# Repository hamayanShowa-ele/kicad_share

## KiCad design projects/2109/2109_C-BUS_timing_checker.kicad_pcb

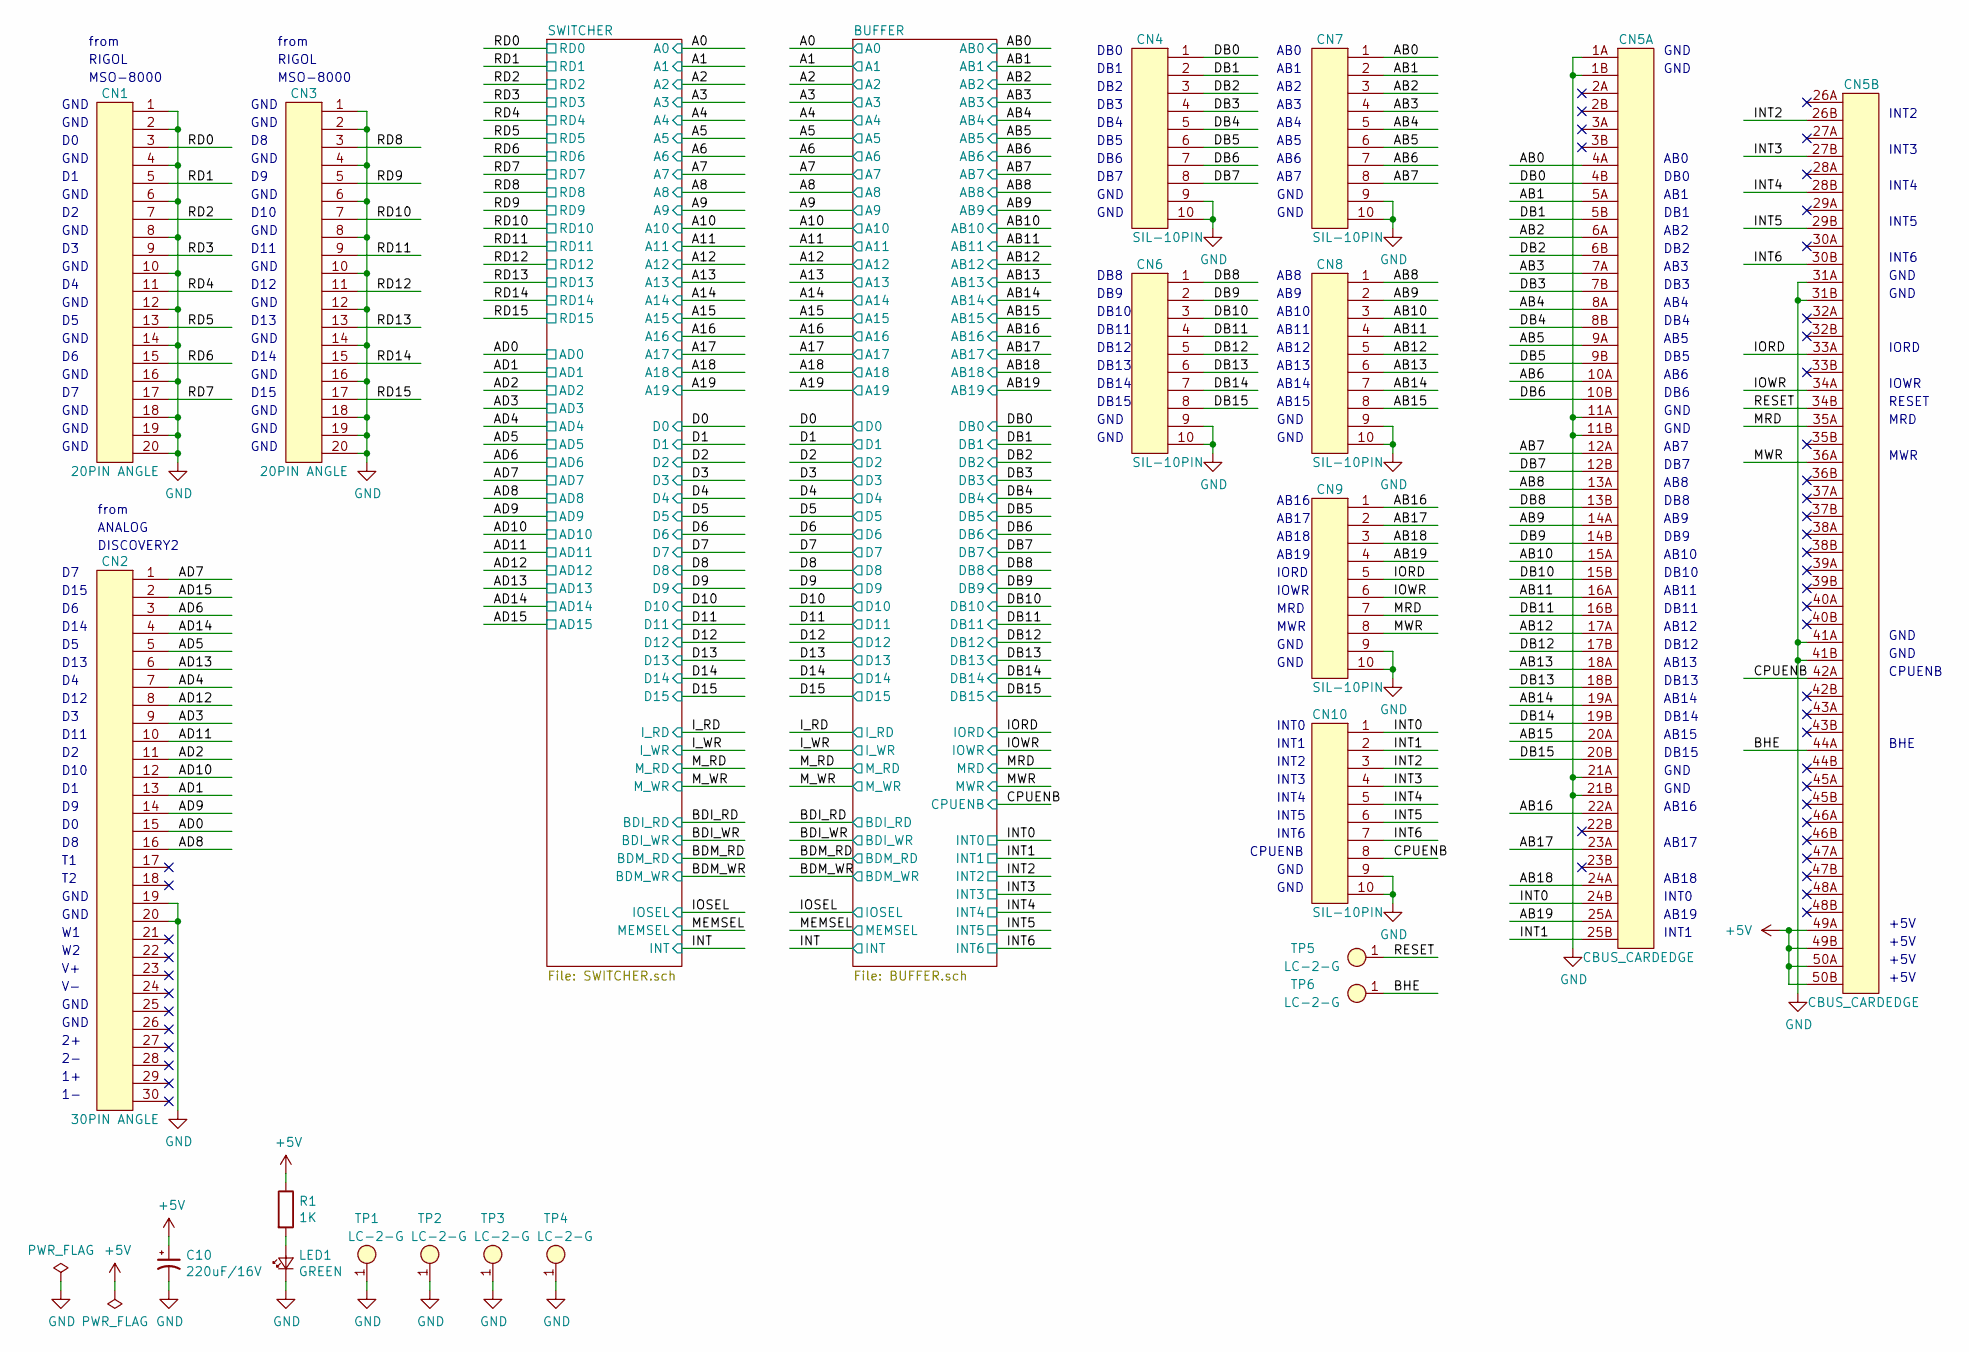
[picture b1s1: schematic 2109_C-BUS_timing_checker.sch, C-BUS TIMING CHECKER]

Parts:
C10: 220uF/16V; CP_Radial_D6.50mm_P2.50mm
CN1, CN3: 20PIN ANGLE; cn_HIF3FC-20PA-254DS
CN2: 30PIN ANGLE; cn_HIF3FC-30PA-254DS
CN4, CN6, CN7, CN8, CN9, CN10: SIL-10PIN; Pin_Header_Straight_1x10_Pitch2.54mm
CN5: CBUS_CARDEDGE; cn_CBUS_CARDEDGE
LED1: GREEN; C_0603
R1: 1K; C_0603
TP1, TP2, TP3, TP4, TP5, TP6: LC-2-G; tp_LC-2-G

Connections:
+5V: C10.1, CN5.49A, CN5.49B, CN5.50A, CN5.50B, R1.1; also elsewhere on the board
/AB0: CN5.4A, CN7.1; also elsewhere on the board
/AB1: CN5.5A, CN7.2; also elsewhere on the board
/AB2: CN5.6A, CN7.3; also elsewhere on the board
/AB3: CN5.7A, CN7.4; also elsewhere on the board
/AB4: CN5.8A, CN7.5; also elsewhere on the board
/AB5: CN5.9A, CN7.6; also elsewhere on the board
/AB6: CN5.10A, CN7.7; also elsewhere on the board
/AB7: CN5.12A, CN7.8; also elsewhere on the board
/AB8: CN5.13A, CN8.1; also elsewhere on the board
/AB9: CN5.14A, CN8.2; also elsewhere on the board
/AB10: CN5.15A, CN8.3; also elsewhere on the board
/AB11: CN5.16A, CN8.4; also elsewhere on the board
/AB12: CN5.17A, CN8.5; also elsewhere on the board
/AB13: CN5.18A, CN8.6; also elsewhere on the board
/AB14: CN5.19A, CN8.7; also elsewhere on the board
/AB15: CN5.20A, CN8.8; also elsewhere on the board
/AB16: CN5.22A, CN9.1; also elsewhere on the board
/AB17: CN5.23A, CN9.2; also elsewhere on the board
/AB18: CN5.24A, CN9.3; also elsewhere on the board
/AB19: CN5.25A, CN9.4; also elsewhere on the board
/AD0: CN2.15; also elsewhere on the board
/AD1: CN2.13; also elsewhere on the board
/AD2: CN2.11; also elsewhere on the board
/AD3: CN2.9; also elsewhere on the board
/AD4: CN2.7; also elsewhere on the board
/AD5: CN2.5; also elsewhere on the board
/AD6: CN2.3; also elsewhere on the board
/AD7: CN2.1; also elsewhere on the board
/AD8: CN2.16; also elsewhere on the board
/AD9: CN2.14; also elsewhere on the board
/AD10: CN2.12; also elsewhere on the board
/AD11: CN2.10; also elsewhere on the board
/AD12: CN2.8; also elsewhere on the board
/AD13: CN2.6; also elsewhere on the board
/AD14: CN2.4; also elsewhere on the board
/AD15: CN2.2; also elsewhere on the board
/BHE: CN5.44A, TP6.1
/CPUENB: CN5.42A, CN10.8; also elsewhere on the board
/DB0: CN4.1, CN5.4B; also elsewhere on the board
/DB1: CN4.2, CN5.5B; also elsewhere on the board
/DB2: CN4.3, CN5.6B; also elsewhere on the board
/DB3: CN4.4, CN5.7B; also elsewhere on the board
/DB4: CN4.5, CN5.8B; also elsewhere on the board
/DB5: CN4.6, CN5.9B; also elsewhere on the board
/DB6: CN4.7, CN5.10B; also elsewhere on the board
/DB7: CN4.8, CN5.12B; also elsewhere on the board
/DB8: CN5.13B, CN6.1; also elsewhere on the board
/DB9: CN5.14B, CN6.2; also elsewhere on the board
/DB10: CN5.15B, CN6.3; also elsewhere on the board
/DB11: CN5.16B, CN6.4; also elsewhere on the board
/DB12: CN5.17B, CN6.5; also elsewhere on the board
/DB13: CN5.18B, CN6.6; also elsewhere on the board
/DB14: CN5.19B, CN6.7; also elsewhere on the board
/DB15: CN5.20B, CN6.8; also elsewhere on the board
/INT0: CN5.24B, CN10.1; also elsewhere on the board
/INT1: CN5.25B, CN10.2; also elsewhere on the board
/INT2: CN5.26B, CN10.3; also elsewhere on the board
/INT3: CN5.27B, CN10.4; also elsewhere on the board
/INT4: CN5.28B, CN10.5; also elsewhere on the board
/INT5: CN5.29B, CN10.6; also elsewhere on the board
/INT6: CN5.30B, CN10.7; also elsewhere on the board
/IORD: CN5.33A, CN9.5; also elsewhere on the board
/IOWR: CN5.34A, CN9.6; also elsewhere on the board
/MRD: CN5.35A, CN9.7; also elsewhere on the board
/MWR: CN5.36A, CN9.8; also elsewhere on the board
/RD0: CN1.3; also elsewhere on the board
/RD1: CN1.5; also elsewhere on the board
/RD2: CN1.7; also elsewhere on the board
/RD3: CN1.9; also elsewhere on the board
/RD4: CN1.11; also elsewhere on the board
/RD5: CN1.13; also elsewhere on the board
/RD6: CN1.15; also elsewhere on the board
/RD7: CN1.17; also elsewhere on the board
/RD8: CN3.3; also elsewhere on the board
/RD9: CN3.5; also elsewhere on the board
/RD10: CN3.7; also elsewhere on the board
/RD11: CN3.9; also elsewhere on the board
/RD12: CN3.11; also elsewhere on the board
/RD13: CN3.13; also elsewhere on the board
/RD14: CN3.15; also elsewhere on the board
/RD15: CN3.17; also elsewhere on the board
/RESET: CN5.34B, TP5.1
GND: C10.2, CN1.1, CN1.2, CN1.4, CN1.6, CN1.8, CN1.10, CN1.12, CN1.14, CN1.16, CN1.18, CN1.19, CN1.20, CN2.19, CN2.20, CN3.1, CN3.2, CN3.4, CN3.6, CN3.8, CN3.10, CN3.12, CN3.14, CN3.16, CN3.18, CN3.19, CN3.20, CN4.9, CN4.10, CN5.1A, CN5.1B, CN5.11A, CN5.11B, CN5.21A, CN5.21B, CN5.31A, CN5.31B, CN5.41A, CN5.41B, CN6.9, CN6.10, CN7.9, CN7.10, CN8.9, CN8.10, CN9.9, CN9.10, CN10.9, CN10.10, LED1.2 (K), TP1.1, TP2.1, TP3.1, TP4.1; also elsewhere on the board
unnamed: LED1.1 (A), R1.2

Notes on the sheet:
GND
+5V
AB0
AB1
DB0
AB2
AB3
AB4
AB5
AB6
AB7
AB8
AB9
AB10
AB11
AB12
AB13
AB14
AB15
AB16
AB17
AB18
AB19
DB1
DB2
DB3
DB4
DB5
DB6
DB7
DB8
DB9
DB10
DB11
DB12
DB13
DB14
DB15
INT1
INT0

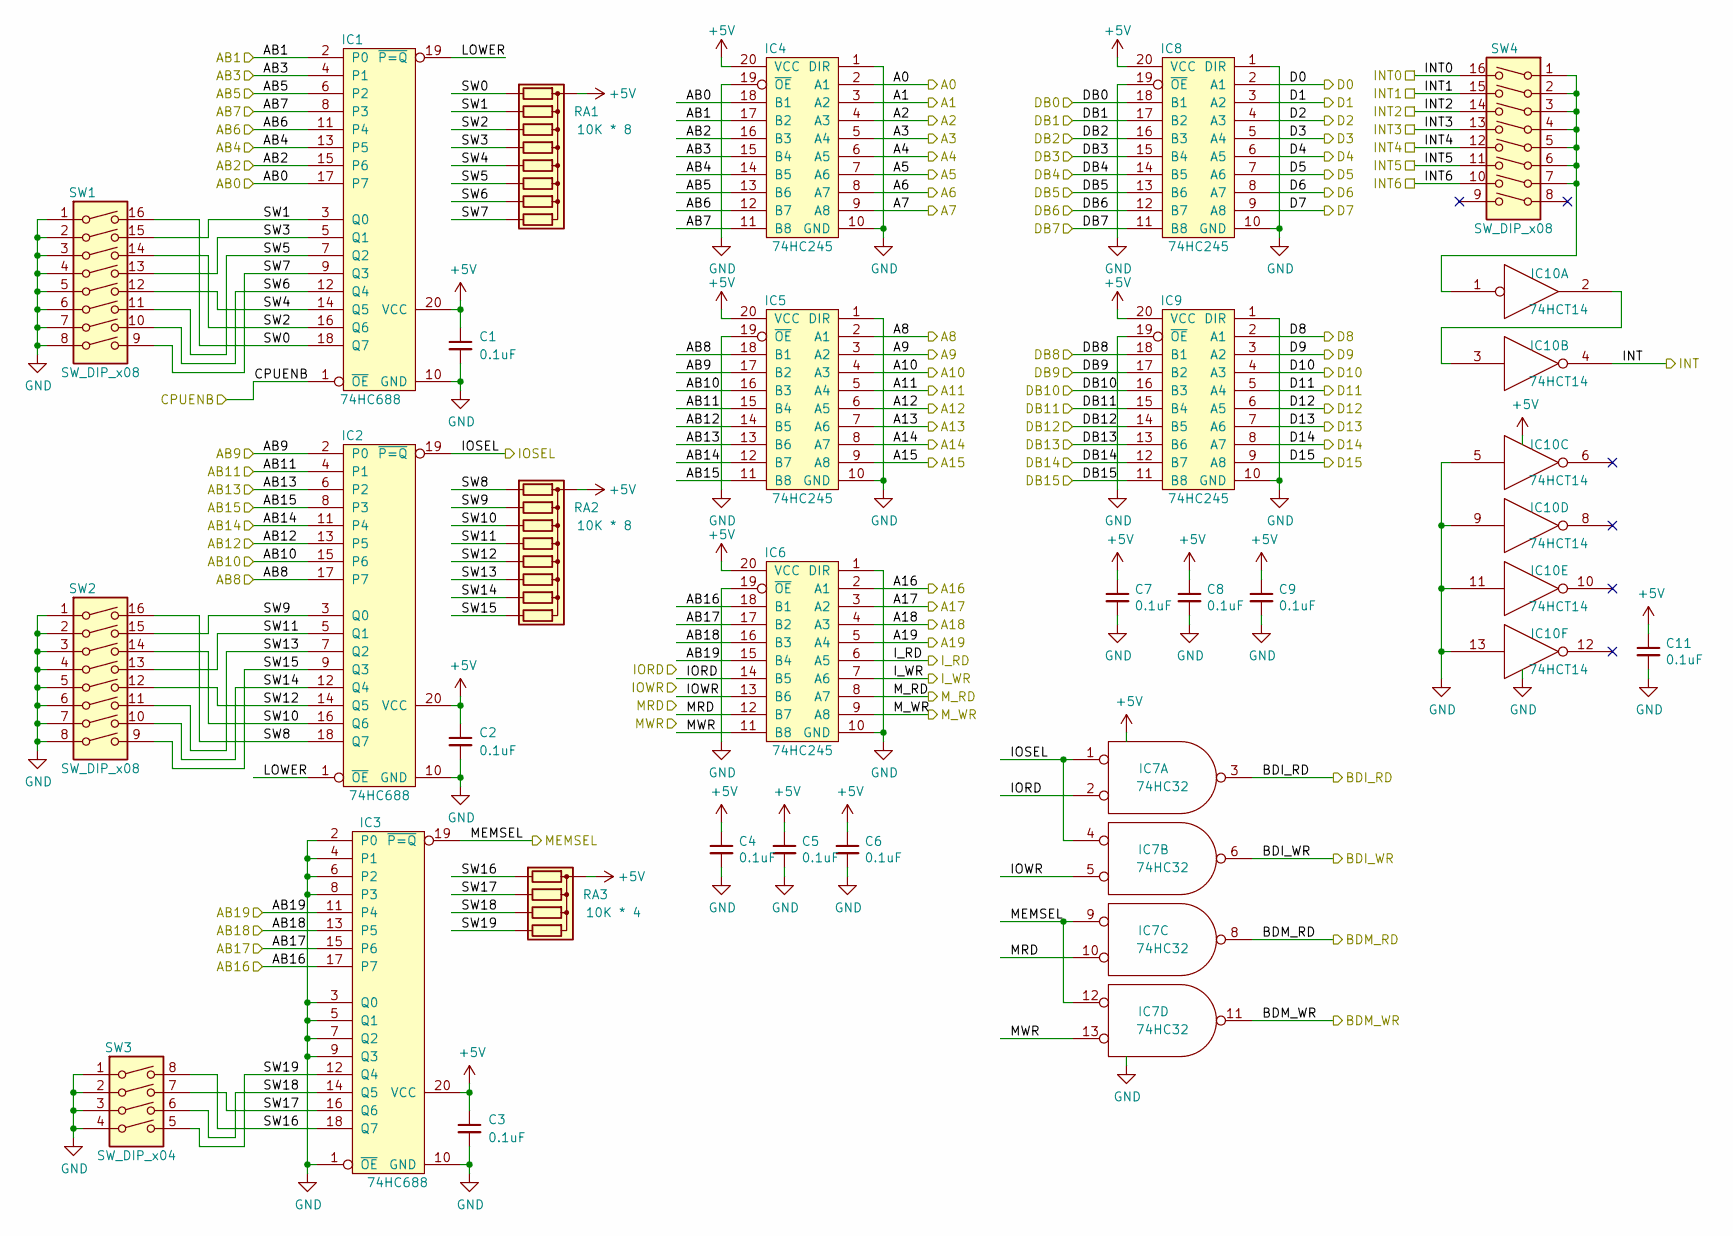
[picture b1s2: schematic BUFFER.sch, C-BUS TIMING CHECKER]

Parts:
C1, C2, C3, C4, C5, C6, C7, C8, C9, C11: 0.1uF; C_0603
IC1, IC2, IC3: 74HC688; ic_DIP-20_W7.62mm
IC4, IC5, IC6, IC8, IC9: 74HC245; ic_DIP-20_W7.62mm
IC7: 74HC32; IC_DIP-14_W7.62mm
IC10: 74HCT14; IC_DIP-14_W7.62mm
RA1, RA2: 10K * 8; ra_RKC1_8B8
RA3: 10K * 4; ra_RKC1_8B4
SW1, SW2, SW4: SW_DIP_x08; ic_DIP-16_W7.62mm
SW3: SW_DIP_x04; ic_DIP-8_W7.62mm

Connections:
+5V: C1.1, C2.1, C3.1, C4.1, C5.1, C6.1, C7.1, C8.1, C9.1, C11.1, IC1.20 (VCC), IC2.20 (VCC), IC3.20 (VCC), IC4.20 (VCC), IC5.20 (VCC), IC6.20 (VCC), IC7.14 (+5V), IC8.20 (VCC), IC9.20 (VCC), IC10.14 (+5V), RA1.1 (common), RA2.1 (common), RA3.1 (common); also elsewhere on the board
/A0: IC4.2 (A1); also elsewhere on the board
/A1: IC4.3 (A2); also elsewhere on the board
/A2: IC4.4 (A3); also elsewhere on the board
/A3: IC4.5 (A4); also elsewhere on the board
/A4: IC4.6 (A5); also elsewhere on the board
/A5: IC4.7 (A6); also elsewhere on the board
/A6: IC4.8 (A7); also elsewhere on the board
/A7: IC4.9 (A8); also elsewhere on the board
/A8: IC5.2 (A1); also elsewhere on the board
/A9: IC5.3 (A2); also elsewhere on the board
/A10: IC5.4 (A3); also elsewhere on the board
/A11: IC5.5 (A4); also elsewhere on the board
/A12: IC5.6 (A5); also elsewhere on the board
/A13: IC5.7 (A6); also elsewhere on the board
/A14: IC5.8 (A7); also elsewhere on the board
/A15: IC5.9 (A8); also elsewhere on the board
/A16: IC6.2 (A1); also elsewhere on the board
/A17: IC6.3 (A2); also elsewhere on the board
/A18: IC6.4 (A3); also elsewhere on the board
/A19: IC6.5 (A4); also elsewhere on the board
/AB0: IC1.17 (P7), IC4.18 (B1); also elsewhere on the board
/AB1: IC1.2 (P0), IC4.17 (B2); also elsewhere on the board
/AB2: IC1.15 (P6), IC4.16 (B3); also elsewhere on the board
/AB3: IC1.4 (P1), IC4.15 (B4); also elsewhere on the board
/AB4: IC1.13 (P5), IC4.14 (B5); also elsewhere on the board
/AB5: IC1.6 (P2), IC4.13 (B6); also elsewhere on the board
/AB6: IC1.11 (P4), IC4.12 (B7); also elsewhere on the board
/AB7: IC1.8 (P3), IC4.11 (B8); also elsewhere on the board
/AB8: IC2.17 (P7), IC5.18 (B1); also elsewhere on the board
/AB9: IC2.2 (P0), IC5.17 (B2); also elsewhere on the board
/AB10: IC2.15 (P6), IC5.16 (B3); also elsewhere on the board
/AB11: IC2.4 (P1), IC5.15 (B4); also elsewhere on the board
/AB12: IC2.13 (P5), IC5.14 (B5); also elsewhere on the board
/AB13: IC2.6 (P2), IC5.13 (B6); also elsewhere on the board
/AB14: IC2.11 (P4), IC5.12 (B7); also elsewhere on the board
/AB15: IC2.8 (P3), IC5.11 (B8); also elsewhere on the board
/AB16: IC3.17 (P7), IC6.18 (B1); also elsewhere on the board
/AB17: IC3.15 (P6), IC6.17 (B2); also elsewhere on the board
/AB18: IC3.13 (P5), IC6.16 (B3); also elsewhere on the board
/AB19: IC3.11 (P4), IC6.15 (B4); also elsewhere on the board
/BDI_RD: IC7.3; also elsewhere on the board
/BDI_WR: IC7.6; also elsewhere on the board
/BDM_RD: IC7.8; also elsewhere on the board
/BDM_WR: IC7.11; also elsewhere on the board
/BUFFER/LOWER: IC1.19 (~P=Q), IC2.1 (~OE)
/BUFFER/SW0: IC1.18 (Q7), RA1.2 (R1), SW1.16
/BUFFER/SW1: IC1.3 (Q0), RA1.3 (R2), SW1.15
/BUFFER/SW2: IC1.16 (Q6), RA1.4 (R3), SW1.14
/BUFFER/SW3: IC1.5 (Q1), RA1.5 (R4), SW1.13
/BUFFER/SW4: IC1.14 (Q5), RA1.6 (R5), SW1.12
/BUFFER/SW5: IC1.7 (Q2), RA1.7 (R6), SW1.11
/BUFFER/SW6: IC1.12 (Q4), RA1.8 (R7), SW1.10
/BUFFER/SW7: IC1.9 (Q3), RA1.9 (R8), SW1.9
/BUFFER/SW8: IC2.18 (Q7), RA2.2 (R1), SW2.16
/BUFFER/SW9: IC2.3 (Q0), RA2.3 (R2), SW2.15
/BUFFER/SW10: IC2.16 (Q6), RA2.4 (R3), SW2.14
/BUFFER/SW11: IC2.5 (Q1), RA2.5 (R4), SW2.13
/BUFFER/SW12: IC2.14 (Q5), RA2.6 (R5), SW2.12
/BUFFER/SW13: IC2.7 (Q2), RA2.7 (R6), SW2.11
/BUFFER/SW14: IC2.12 (Q4), RA2.8 (R7), SW2.10
/BUFFER/SW15: IC2.9 (Q3), RA2.9 (R8), SW2.9
/BUFFER/SW16: IC3.18 (Q7), RA3.2 (R1), SW3.8
/BUFFER/SW17: IC3.16 (Q6), RA3.3 (R2), SW3.7
/BUFFER/SW18: IC3.14 (Q5), RA3.4 (R3), SW3.6
/BUFFER/SW19: IC3.12 (Q4), RA3.5 (R4), SW3.5
/CPUENB: IC1.1 (~OE); also elsewhere on the board
/D0: IC8.2 (A1); also elsewhere on the board
/D1: IC8.3 (A2); also elsewhere on the board
/D2: IC8.4 (A3); also elsewhere on the board
/D3: IC8.5 (A4); also elsewhere on the board
/D4: IC8.6 (A5); also elsewhere on the board
/D5: IC8.7 (A6); also elsewhere on the board
/D6: IC8.8 (A7); also elsewhere on the board
/D7: IC8.9 (A8); also elsewhere on the board
/D8: IC9.2 (A1); also elsewhere on the board
/D9: IC9.3 (A2); also elsewhere on the board
/D10: IC9.4 (A3); also elsewhere on the board
/D11: IC9.5 (A4); also elsewhere on the board
/D12: IC9.6 (A5); also elsewhere on the board
/D13: IC9.7 (A6); also elsewhere on the board
/D14: IC9.8 (A7); also elsewhere on the board
/D15: IC9.9 (A8); also elsewhere on the board
/DB0: IC8.18 (B1); also elsewhere on the board
/DB1: IC8.17 (B2); also elsewhere on the board
/DB2: IC8.16 (B3); also elsewhere on the board
/DB3: IC8.15 (B4); also elsewhere on the board
/DB4: IC8.14 (B5); also elsewhere on the board
/DB5: IC8.13 (B6); also elsewhere on the board
/DB6: IC8.12 (B7); also elsewhere on the board
/DB7: IC8.11 (B8); also elsewhere on the board
/DB8: IC9.18 (B1); also elsewhere on the board
/DB9: IC9.17 (B2); also elsewhere on the board
/DB10: IC9.16 (B3); also elsewhere on the board
/DB11: IC9.15 (B4); also elsewhere on the board
/DB12: IC9.14 (B5); also elsewhere on the board
/DB13: IC9.13 (B6); also elsewhere on the board
/DB14: IC9.12 (B7); also elsewhere on the board
/DB15: IC9.11 (B8); also elsewhere on the board
/INT: IC10.4; also elsewhere on the board
/INT0: SW4.16; also elsewhere on the board
/INT1: SW4.15; also elsewhere on the board
/INT2: SW4.14; also elsewhere on the board
/INT3: SW4.13; also elsewhere on the board
/INT4: SW4.12; also elsewhere on the board
/INT5: SW4.11; also elsewhere on the board
/INT6: SW4.10; also elsewhere on the board
/IORD: IC6.14 (B5), IC7.2; also elsewhere on the board
/IOSEL: IC2.19 (~P=Q), IC7.1, IC7.4; also elsewhere on the board
/IOWR: IC6.13 (B6), IC7.5; also elsewhere on the board
/I_RD: IC6.6 (A5); also elsewhere on the board
/I_WR: IC6.7 (A6); also elsewhere on the board
/MEMSEL: IC3.19 (~P=Q), IC7.9, IC7.12; also elsewhere on the board
/MRD: IC6.12 (B7), IC7.10; also elsewhere on the board
/MWR: IC6.11 (B8), IC7.13; also elsewhere on the board
/M_RD: IC6.8 (A7); also elsewhere on the board
/M_WR: IC6.9 (A8); also elsewhere on the board
GND: C1.2, C2.2, C3.2, C4.2, C5.2, C6.2, C7.2, C8.2, C9.2, C11.2, IC1.10 (GND), IC2.10 (GND), IC3.1 (~OE), IC3.2 (P0), IC3.3 (Q0), IC3.4 (P1), IC3.5 (Q1), IC3.6 (P2), IC3.7 (Q2), IC3.8 (P3), IC3.9 (Q3), IC3.10 (GND), IC4.1 (DIR), IC4.10 (GND), IC4.19 (~OE), IC5.1 (DIR), IC5.10 (GND), IC5.19 (~OE), IC6.1 (DIR), IC6.10 (GND), IC6.19 (~OE), IC7.7 (GND), IC8.1 (DIR), IC8.10 (GND), IC8.19 (~OE), IC9.1 (DIR), IC9.10 (GND), IC9.19 (~OE), IC10.5, IC10.7 (GND), IC10.9, IC10.11, IC10.13, SW1.1, SW1.2, SW1.3, SW1.4, SW1.5, SW1.6, SW1.7, SW1.8, SW2.1, SW2.2, SW2.3, SW2.4, SW2.5, SW2.6, SW2.7, SW2.8, SW3.1, SW3.2, SW3.3, SW3.4; also elsewhere on the board
unnamed: IC10.1, SW4.1, SW4.2, SW4.3, SW4.4, SW4.5, SW4.6, SW4.7
unnamed: IC10.2, IC10.3

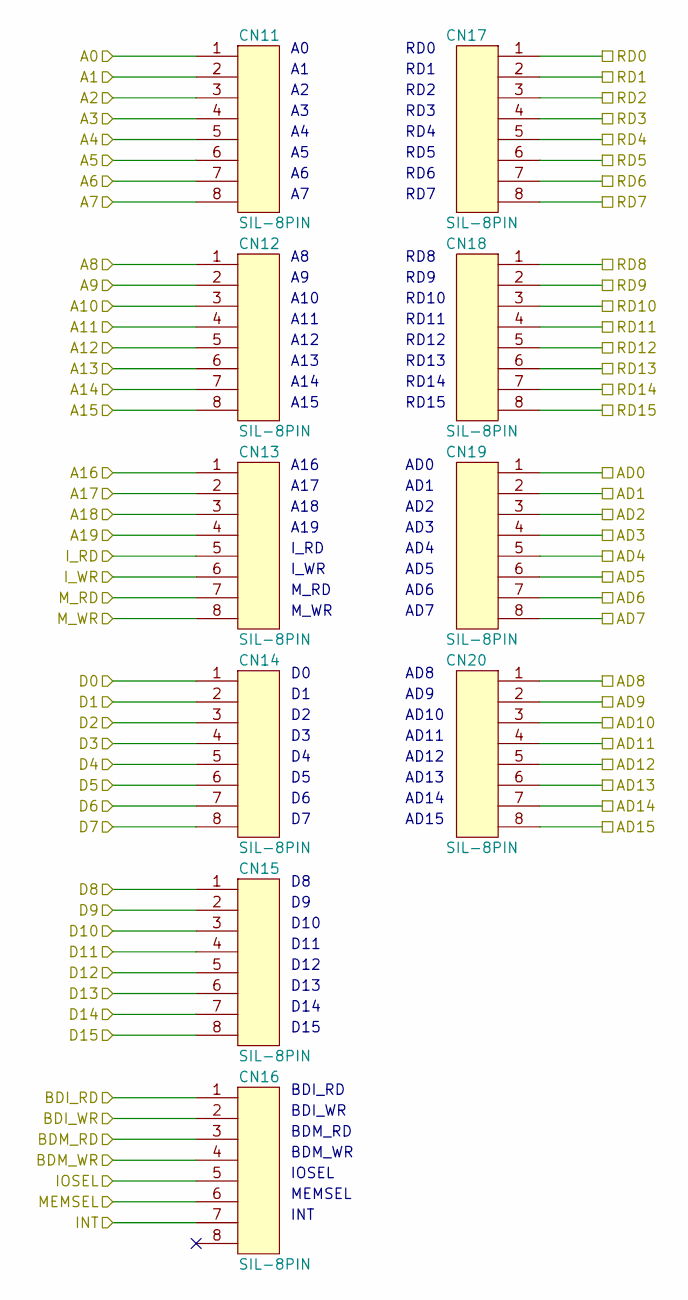
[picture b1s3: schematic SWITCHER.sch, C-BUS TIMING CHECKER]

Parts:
CN11, CN12, CN13, CN14, CN15, CN16, CN17, CN18, CN19, CN20: SIL-8PIN; Pin_Header_Straight_1x08_Pitch2.54mm

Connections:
/A0: CN11.1; also elsewhere on the board
/A1: CN11.2; also elsewhere on the board
/A2: CN11.3; also elsewhere on the board
/A3: CN11.4; also elsewhere on the board
/A4: CN11.5; also elsewhere on the board
/A5: CN11.6; also elsewhere on the board
/A6: CN11.7; also elsewhere on the board
/A7: CN11.8; also elsewhere on the board
/A8: CN12.1; also elsewhere on the board
/A9: CN12.2; also elsewhere on the board
/A10: CN12.3; also elsewhere on the board
/A11: CN12.4; also elsewhere on the board
/A12: CN12.5; also elsewhere on the board
/A13: CN12.6; also elsewhere on the board
/A14: CN12.7; also elsewhere on the board
/A15: CN12.8; also elsewhere on the board
/A16: CN13.1; also elsewhere on the board
/A17: CN13.2; also elsewhere on the board
/A18: CN13.3; also elsewhere on the board
/A19: CN13.4; also elsewhere on the board
/AD0: CN19.1; also elsewhere on the board
/AD1: CN19.2; also elsewhere on the board
/AD2: CN19.3; also elsewhere on the board
/AD3: CN19.4; also elsewhere on the board
/AD4: CN19.5; also elsewhere on the board
/AD5: CN19.6; also elsewhere on the board
/AD6: CN19.7; also elsewhere on the board
/AD7: CN19.8; also elsewhere on the board
/AD8: CN20.1; also elsewhere on the board
/AD9: CN20.2; also elsewhere on the board
/AD10: CN20.3; also elsewhere on the board
/AD11: CN20.4; also elsewhere on the board
/AD12: CN20.5; also elsewhere on the board
/AD13: CN20.6; also elsewhere on the board
/AD14: CN20.7; also elsewhere on the board
/AD15: CN20.8; also elsewhere on the board
/BDI_RD: CN16.1; also elsewhere on the board
/BDI_WR: CN16.2; also elsewhere on the board
/BDM_RD: CN16.3; also elsewhere on the board
/BDM_WR: CN16.4; also elsewhere on the board
/D0: CN14.1; also elsewhere on the board
/D1: CN14.2; also elsewhere on the board
/D2: CN14.3; also elsewhere on the board
/D3: CN14.4; also elsewhere on the board
/D4: CN14.5; also elsewhere on the board
/D5: CN14.6; also elsewhere on the board
/D6: CN14.7; also elsewhere on the board
/D7: CN14.8; also elsewhere on the board
/D8: CN15.1; also elsewhere on the board
/D9: CN15.2; also elsewhere on the board
/D10: CN15.3; also elsewhere on the board
/D11: CN15.4; also elsewhere on the board
/D12: CN15.5; also elsewhere on the board
/D13: CN15.6; also elsewhere on the board
/D14: CN15.7; also elsewhere on the board
/D15: CN15.8; also elsewhere on the board
/INT: CN16.7; also elsewhere on the board
/IOSEL: CN16.5; also elsewhere on the board
/I_RD: CN13.5; also elsewhere on the board
/I_WR: CN13.6; also elsewhere on the board
/MEMSEL: CN16.6; also elsewhere on the board
/M_RD: CN13.7; also elsewhere on the board
/M_WR: CN13.8; also elsewhere on the board
/RD0: CN17.1; also elsewhere on the board
/RD1: CN17.2; also elsewhere on the board
/RD2: CN17.3; also elsewhere on the board
/RD3: CN17.4; also elsewhere on the board
/RD4: CN17.5; also elsewhere on the board
/RD5: CN17.6; also elsewhere on the board
/RD6: CN17.7; also elsewhere on the board
/RD7: CN17.8; also elsewhere on the board
/RD8: CN18.1; also elsewhere on the board
/RD9: CN18.2; also elsewhere on the board
/RD10: CN18.3; also elsewhere on the board
/RD11: CN18.4; also elsewhere on the board
/RD12: CN18.5; also elsewhere on the board
/RD13: CN18.6; also elsewhere on the board
/RD14: CN18.7; also elsewhere on the board
/RD15: CN18.8; also elsewhere on the board

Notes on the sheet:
RD0
RD1
RD2
RD3
RD4
RD5
RD6
RD7
RD8
RD9
RD10
RD11
RD12
RD13
RD14
RD15
A10
A11
A12
A13
A14
A15
A16
A17
A18
A19
I_RD
I_WR
M_RD
M_WR
D10
D11
D12
D13
D14
D15
BDI_RD
BDI_WR
BDM_RD
BDM_WR

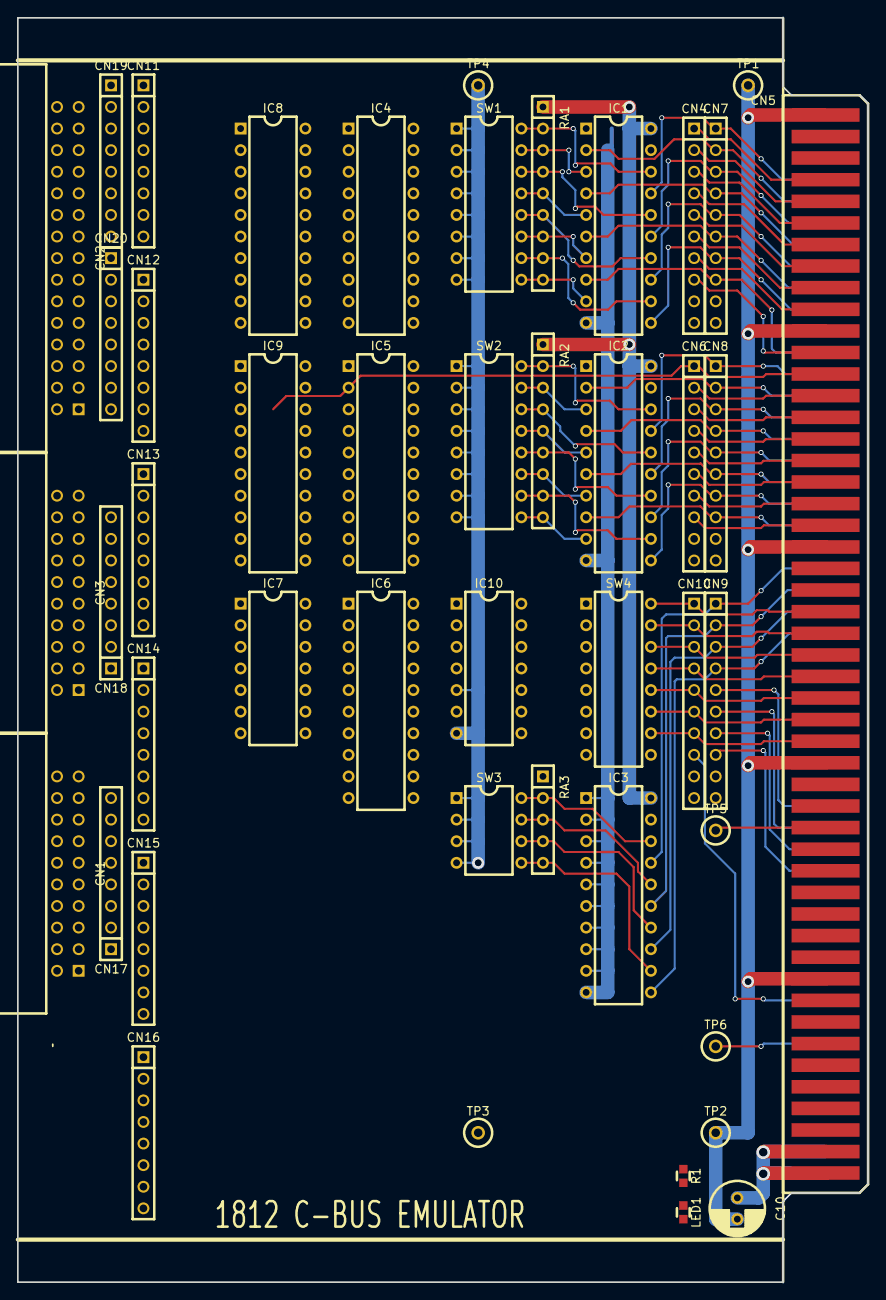
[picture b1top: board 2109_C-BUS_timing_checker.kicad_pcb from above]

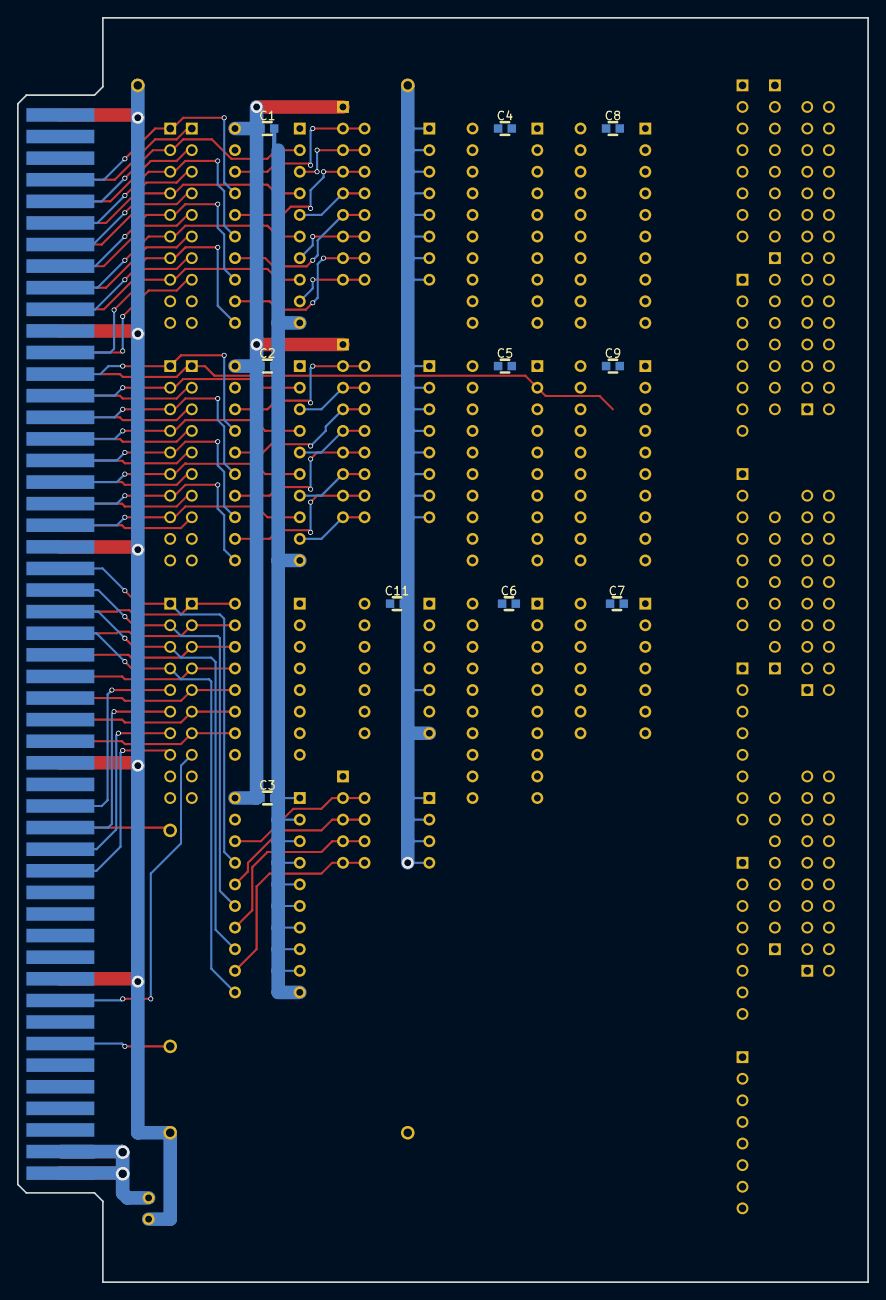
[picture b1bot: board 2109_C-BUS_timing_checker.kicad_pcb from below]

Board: 2 copper layers, 100.0 x 148.7 mm, 56 parts (10 on the bottom side), 155 nets.

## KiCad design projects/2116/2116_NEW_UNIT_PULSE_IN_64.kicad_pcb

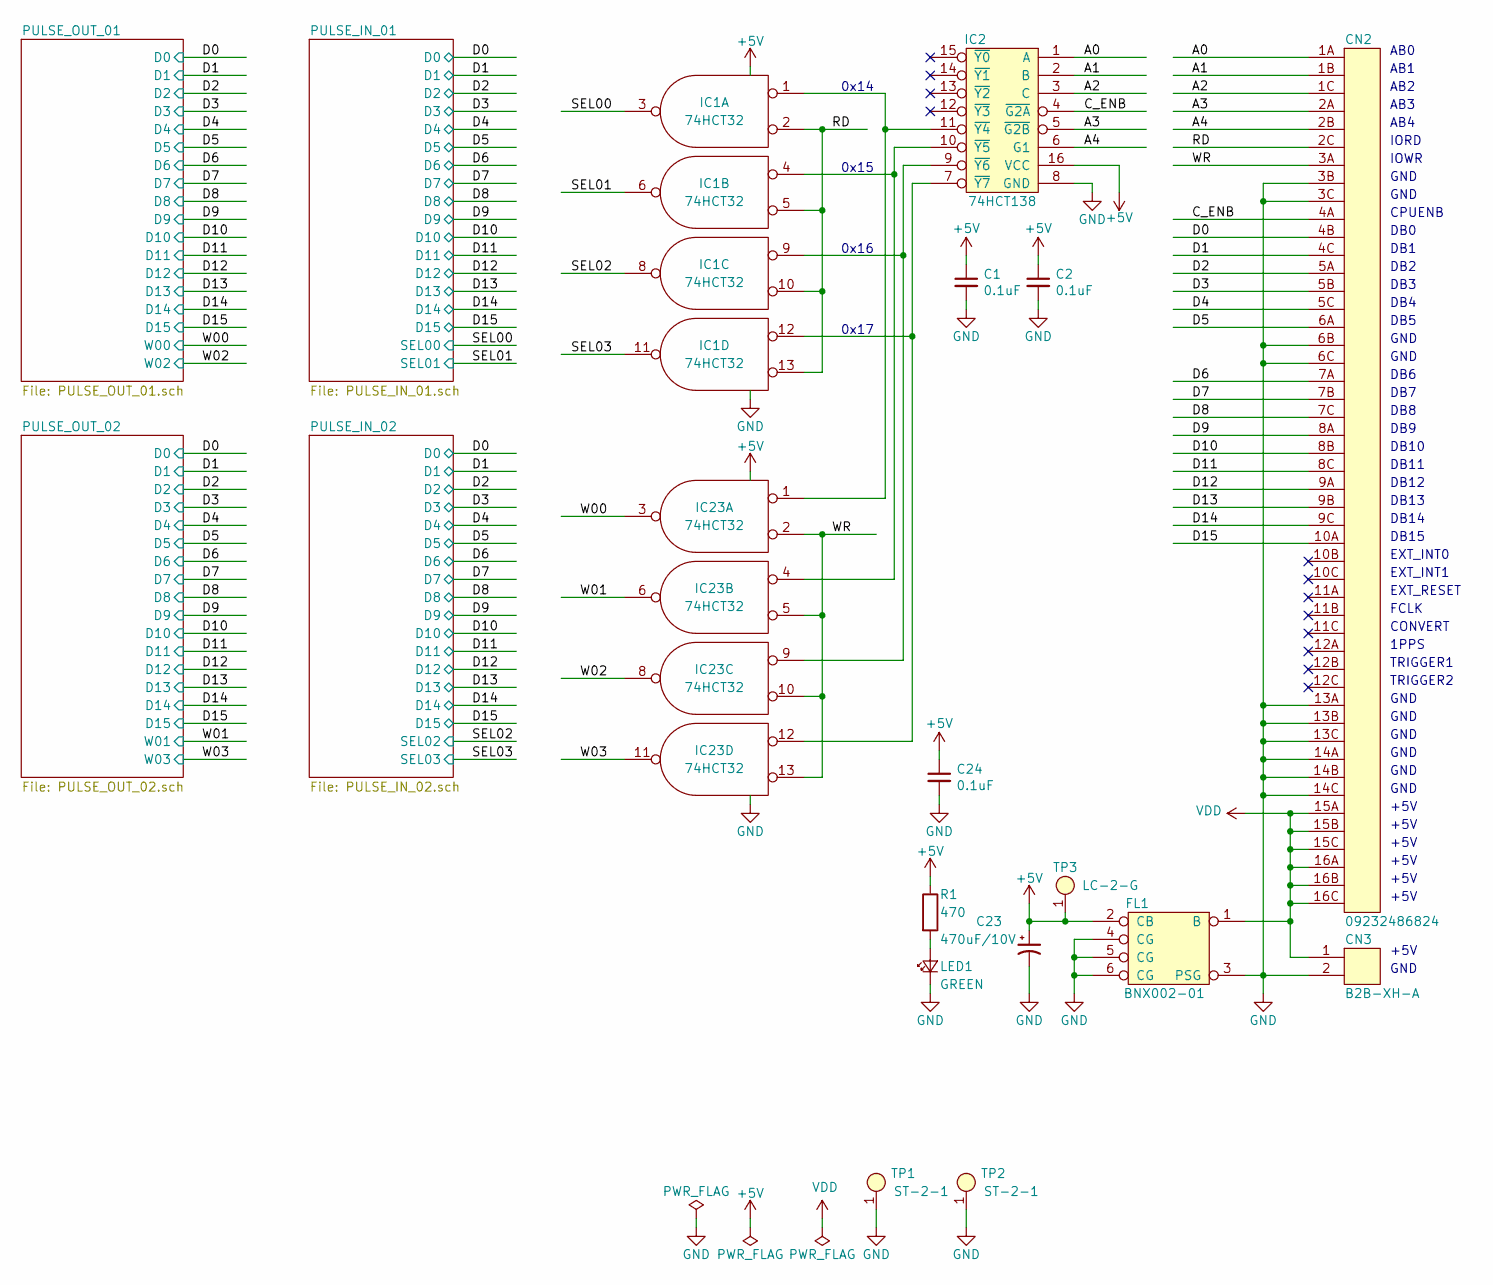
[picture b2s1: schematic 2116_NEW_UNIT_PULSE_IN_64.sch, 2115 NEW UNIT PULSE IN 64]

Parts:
C1, C2, C24: 0.1uF; C_0603
C23: 470uF/10V; CP_D8_P3R5
CN2: 09232486824; cn_09282486801
CN3: B2B-XH-A; cn_B2B-XH-A
FL1: BNX002-01
IC1, IC23: 74HCT32; IC_DIP-14_W7.62mm
IC2: 74HCT138; ic_DIP-16_W7.62mm
LED1: GREEN; LED_D3.0mm_center
R1: 470; R_TH_5R08
TP1, TP2: ST-2-1; LC-2-G
TP3: LC-2-G

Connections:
+5V: C1.1, C2.1, C23.1, C24.1, FL1.2 (CB), IC1.14 (+5V), IC2.16 (VCC), IC23.14 (+5V), R1.1, TP3.1; also elsewhere on the board
/A0: CN2.1A, IC2.1 (A)
/A1: CN2.1B, IC2.2 (B)
/A2: CN2.1C, IC2.3 (C)
/A3: CN2.2A, IC2.5 (~G2B)
/A4: CN2.2B, IC2.6 (G1)
/C_ENB: CN2.4A, IC2.4 (~G2A)
/D0: CN2.4B; also elsewhere on the board
/D1: CN2.4C; also elsewhere on the board
/D2: CN2.5A; also elsewhere on the board
/D3: CN2.5B; also elsewhere on the board
/D4: CN2.5C; also elsewhere on the board
/D5: CN2.6A; also elsewhere on the board
/D6: CN2.7A; also elsewhere on the board
/D7: CN2.7B; also elsewhere on the board
/D8: CN2.7C; also elsewhere on the board
/D9: CN2.8A; also elsewhere on the board
/D10: CN2.8B; also elsewhere on the board
/D11: CN2.8C; also elsewhere on the board
/D12: CN2.9A; also elsewhere on the board
/D13: CN2.9B; also elsewhere on the board
/D14: CN2.9C; also elsewhere on the board
/D15: CN2.10A; also elsewhere on the board
/RD: CN2.2C, IC1.2, IC1.5, IC1.10, IC1.13
/SEL00: IC1.3; also elsewhere on the board
/SEL01: IC1.6; also elsewhere on the board
/SEL02: IC1.8; also elsewhere on the board
/SEL03: IC1.11; also elsewhere on the board
/W00: IC23.3; also elsewhere on the board
/W01: IC23.6; also elsewhere on the board
/W02: IC23.8; also elsewhere on the board
/W03: IC23.11; also elsewhere on the board
/WR: CN2.3A, IC23.2, IC23.5, IC23.10, IC23.13
GND: C1.2, C2.2, C23.2, C24.2, CN2.3B, CN2.3C, CN2.6B, CN2.6C, CN2.13A, CN2.13B, CN2.13C, CN2.14A, CN2.14B, CN2.14C, CN3.2, FL1.3 (PSG), FL1.4 (CG), FL1.5 (CG), FL1.6 (CG), IC1.7 (GND), IC2.8 (GND), IC23.7 (GND), LED1.2 (K), TP1.1, TP2.1; also elsewhere on the board
unnamed: IC1.1, IC2.11 (~Y4), IC23.1
unnamed: IC1.4, IC2.10 (~Y5), IC23.4
unnamed: IC1.9, IC2.9 (~Y6), IC23.9
unnamed: IC1.12, IC2.7 (~Y7), IC23.12
unnamed: LED1.1 (A), R1.2
VDD: CN2.15A, CN2.15B, CN2.15C, CN2.16A, CN2.16B, CN2.16C, CN3.1, FL1.1 (B)

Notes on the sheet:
AB0
AB1
AB2
AB3
AB4
GND
IORD
IOWR
CPUENB
EXT_INT0
EXT_INT1
EXT_RESET
DB0
DB1
DB2
DB3
DB4
DB5
DB6
DB7
DB8
DB9
DB10
DB11
DB12
DB13
DB14
DB15
+5V
CONVERT
FCLK
1PPS
TRIGGER1
TRIGGER2
0x14
0x15
0x16
0x17
